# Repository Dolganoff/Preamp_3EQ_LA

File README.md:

Copyright Alexei Dolganov (http://www.dolganoff.com)

Definitions
-----------

Here, "Documentation" means schematic diagrams, designs, circuit or circuit
board layouts, mechanical drawings, flow charts and descriptive text,
and other explanatory material.

Legal stuff
-----------

This documentation describes Open Hardware product and is licensed under the
CERN OHL 1.2 (see files LICENSE and cern_ohl_v_1_2_howto-1.pdf for more details 
on designs usage and redistribution.

You may redistribute and modify this documentation under the terms of the
CERN OHL 1.2. (http://ohwr.org/cernohl). 

This documentation is distributed WITHOUT ANY EXPRESS OR IMPLIED WARRANTY, 
INCLUDING OF MERCHANTABILITY, SATISFACTORY QUALITY AND FITNESS FOR A 
PARTICULAR PURPOSE. Please see the CERN OHL v.1.2 for applicable conditions.

You're allowed to use this documentation for free and to build the described 
product and even commercialise it **as long as you comply with the license**.
You must redistribute the documentaion with your product under the same
license terms. 

Notification
------------

You're not obliged to do so but I ask you to let me know if you're building
described product for your own use or commersialise it. 

Software tools used in this project:
------------------------------------

* LTSpice (http://www.linear.com/ltspice) - circuit simulations 
  (source files: *.asc)
  LTSpice is a closed source tool but provided free of charge by Linear.  
* Kicad (http://www.kicad-pcb.org) - EDA design tool - schematics capture, PCB 
  production. Any Kicad version   superior to BZR-5000 can be used to open the 
  designs. Kicad is free and available as open source under GPL v2 license.

Folder Structure
----------------

If you've downloaded this documentation as a complete zip package, you'll
see the following folders inside:

root: 
  README.md: this file  
  LICENSE: license terms  
  cern_ohl_v_1_2_howto-1.pdf: guide on licence usage

src:
  documentation sources including schematics, pcb layout and fabrication plots

src/simulations: 
  circuit simulations

src/kicad-250K-G-v2: 
  kicad project and fab plots for preamp, 250K pots, guitar version

src/kicad-100K-G-v2: 
  kicad project and fab plots for preamp, 100K pots, guitar version

src/kicad-250K-B-v2: 
  kicad project and fab plots for preamp, 250K pots, bass version

src/kicad-100K-B-v2: 
  kicad project and fab plots for preamp, 100K pots, bass version
  
If you've obtained this documentation from github repositoty, you'll
see few additional folders:

download:
	latest download zip package

old_do_not_use:
	old files, do not use these ;)

scripts:
  zip package creation scripts
  
Fabrication files
-----------------

I include standard Gerber files in src/kicad*/plots/plots.zip package
You can send these directly to pcb manufacturer for production. The package
was tested with oshpark and itead, other fab houses may ask for different file
names or formats.

Contact
-------

For all the questions, please contact me (Alexei Dolganov, the author) at 
http://www.dolganoff.com/fr/a-propos/ or message my facebook page
https://www.facebook.com/pages/Dolganoff-Makes-Things/1474869009403564?sk=info

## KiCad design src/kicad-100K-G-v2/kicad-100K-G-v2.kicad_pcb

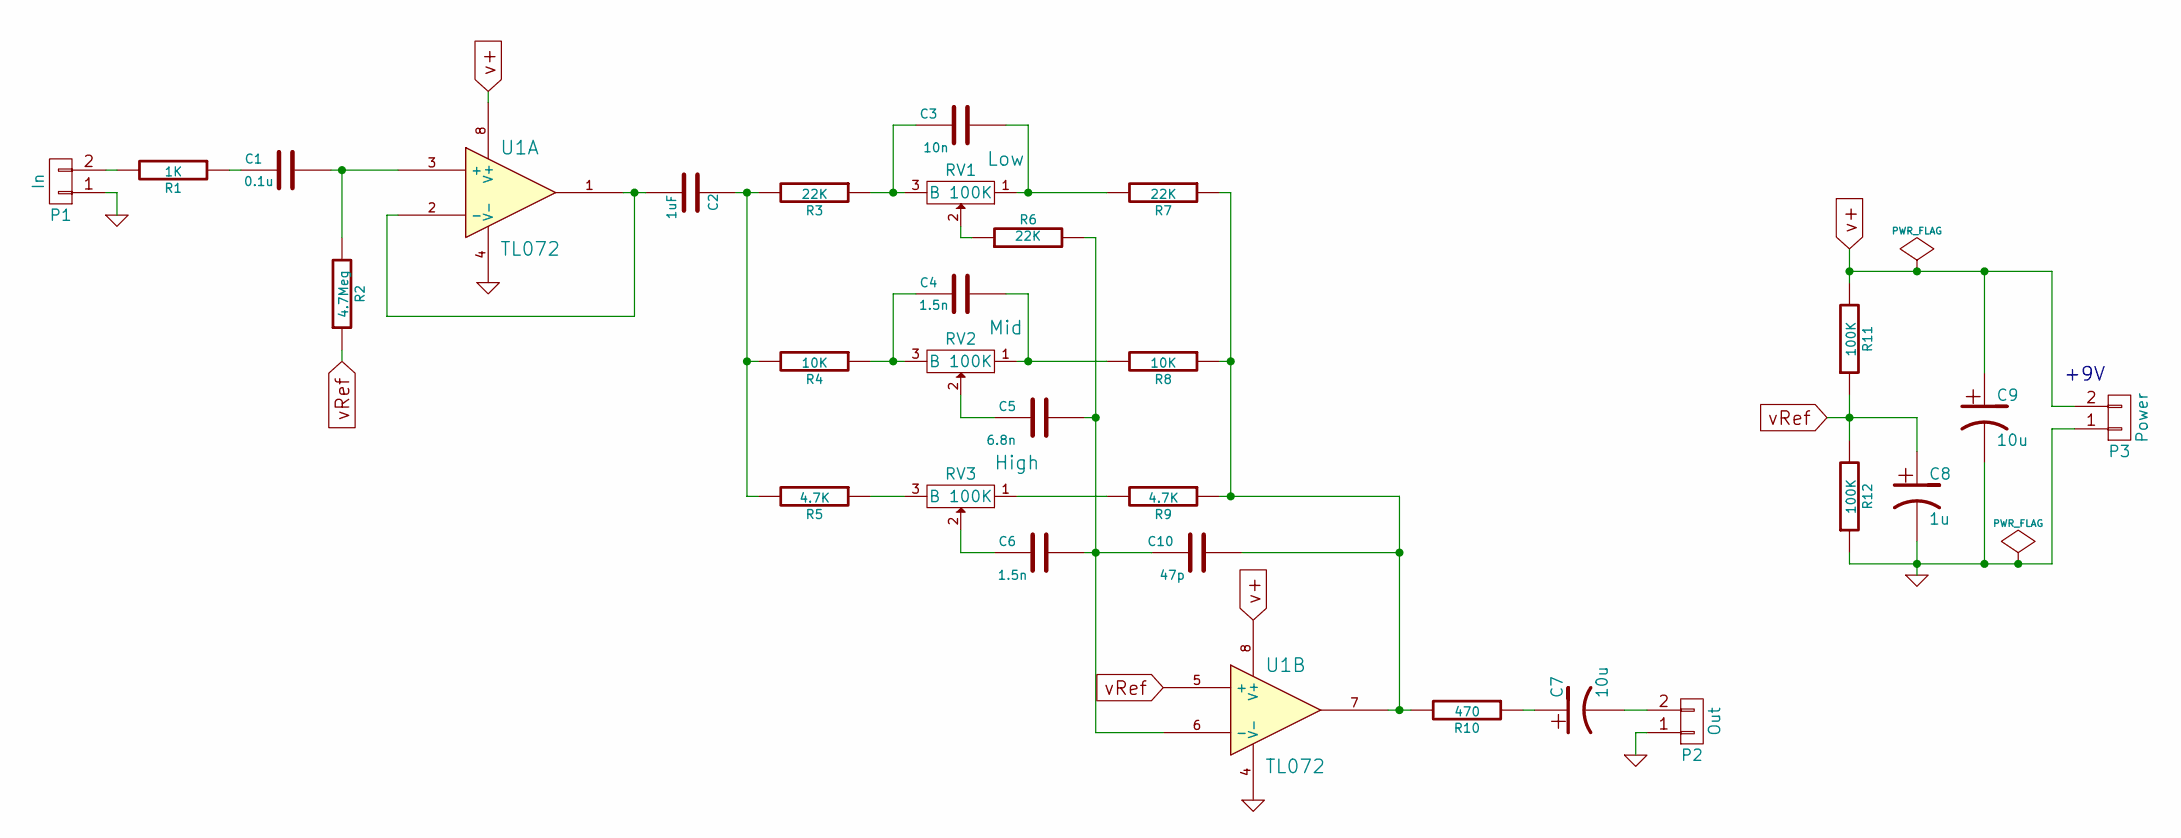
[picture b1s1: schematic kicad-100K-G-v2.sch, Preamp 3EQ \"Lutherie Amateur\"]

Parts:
C1: 0.1u; C2-LARGE_PADS
C2: 1uF; C2-LARGE_PADS
C3: 10n; C2-LARGE_PADS
C4, C6: 1.5n; C2-LARGE_PADS
C5: 6.8n; C2-LARGE_PADS
C7, C9: 10u; C1V5-LARGE_PADS
C8: 1u; C1V5-LARGE_PADS
C10: 47p; C2-LARGE_PADS
P1: In; SIL-2-LARGE_PADS
P2: Out; SIL-2-LARGE_PADS
P3: Power; SIL-2-LARGE_PADS
R1: 1K; R3-LARGE_PADS
R2: 4.7Meg; R3-LARGE_PADS
R3, R6, R7: 22K; R3-LARGE_PADS
R4, R8: 10K; R3-LARGE_PADS
R5, R9: 4.7K; R3-LARGE_PADS
R10: 470; R3-LARGE_PADS
R11, R12: 100K; R3-LARGE_PADS
RV1, RV2, RV3: B 100K; SIL-3-LARGE_PADS
U1: TL072; DIP-8_LARGE_PADS

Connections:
GND: C8.2, C9.2, P1.1, P2.1, P3.1, R12.1, U1.4 (V-)
unnamed: C1.1, R1.1
unnamed: C1.2, R2.2, U1.3 (+)
unnamed: C2.1, R3.2, R4.2, R5.2
unnamed: C2.2, U1.1, U1.2 (-)
unnamed: C3.1, R3.1, RV1.3
unnamed: C3.2, R7.2, RV1.1
unnamed: C4.1, R4.1, RV2.3
unnamed: C4.2, R8.2, RV2.1
unnamed: C5.1, RV2.2
unnamed: C6.1, RV3.2
unnamed: C7.1, R10.1
unnamed: C7.2, P2.2
unnamed: C5.2, C6.2, C10.1, R6.2, U1.6 (-)
unnamed: C10.2, R7.1, R8.1, R9.1, R10.2, U1.7
unnamed: P1.2, R1.2
unnamed: R5.1, RV3.3
unnamed: R6.1, RV1.2
unnamed: R9.2, RV3.1
v+: C9.1, P3.2, R11.2, U1.8 (V+)
vRef: C8.1, R2.1, R11.1, R12.2, U1.5 (+)

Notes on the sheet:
+9V

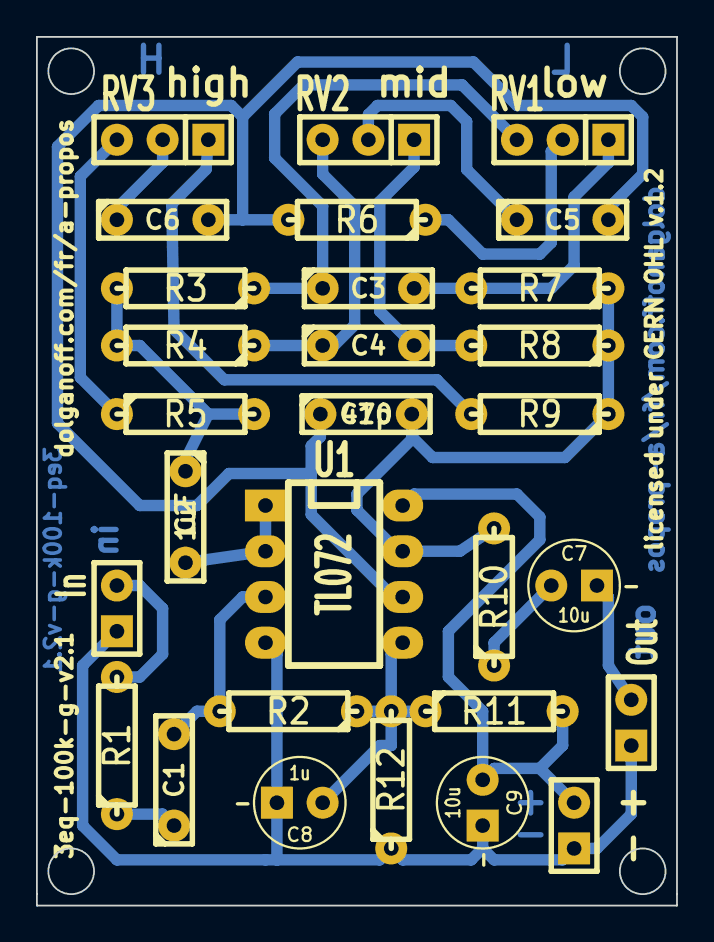
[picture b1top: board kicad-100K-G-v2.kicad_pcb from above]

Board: 2 copper layers, 35.6 x 48.3 mm, 29 parts (0 on the bottom side), 21 nets.

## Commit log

2014-08-27 initial commit: schematics
2014-08-27 started pcb layout
2014-08-27 pcb routed
2014-08-27 routing corrections
2014-08-27 old files cleanup
2014-08-27 sims cleanup
2014-08-29 pcb and plots updated, folder reorg
2014-08-29 README modified
2014-08-29 plots.bat script
2014-08-29 make plots and download bat scripts
2014-09-01 final 2014-07-01
2014-09-01 corrections 2014-09-01
2014-09-28 28/09/2014 minor changes
2014-10-12 changes in bass version
2014-10-12 new download zip
2014-10-29 29/10/2014 corrections to 100K-G: version 2.1
2021-08-29 latest mods

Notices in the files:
src/kicad-100K-G-v2/kicad-100K-G-v2.kicad_pcb:
licensed under CERN OHL v.1.2
src/kicad-100K-G-v2/kicad-100K-G-v2.sch:
Open Hardware, Licensed under CERN OHL v.1.2
